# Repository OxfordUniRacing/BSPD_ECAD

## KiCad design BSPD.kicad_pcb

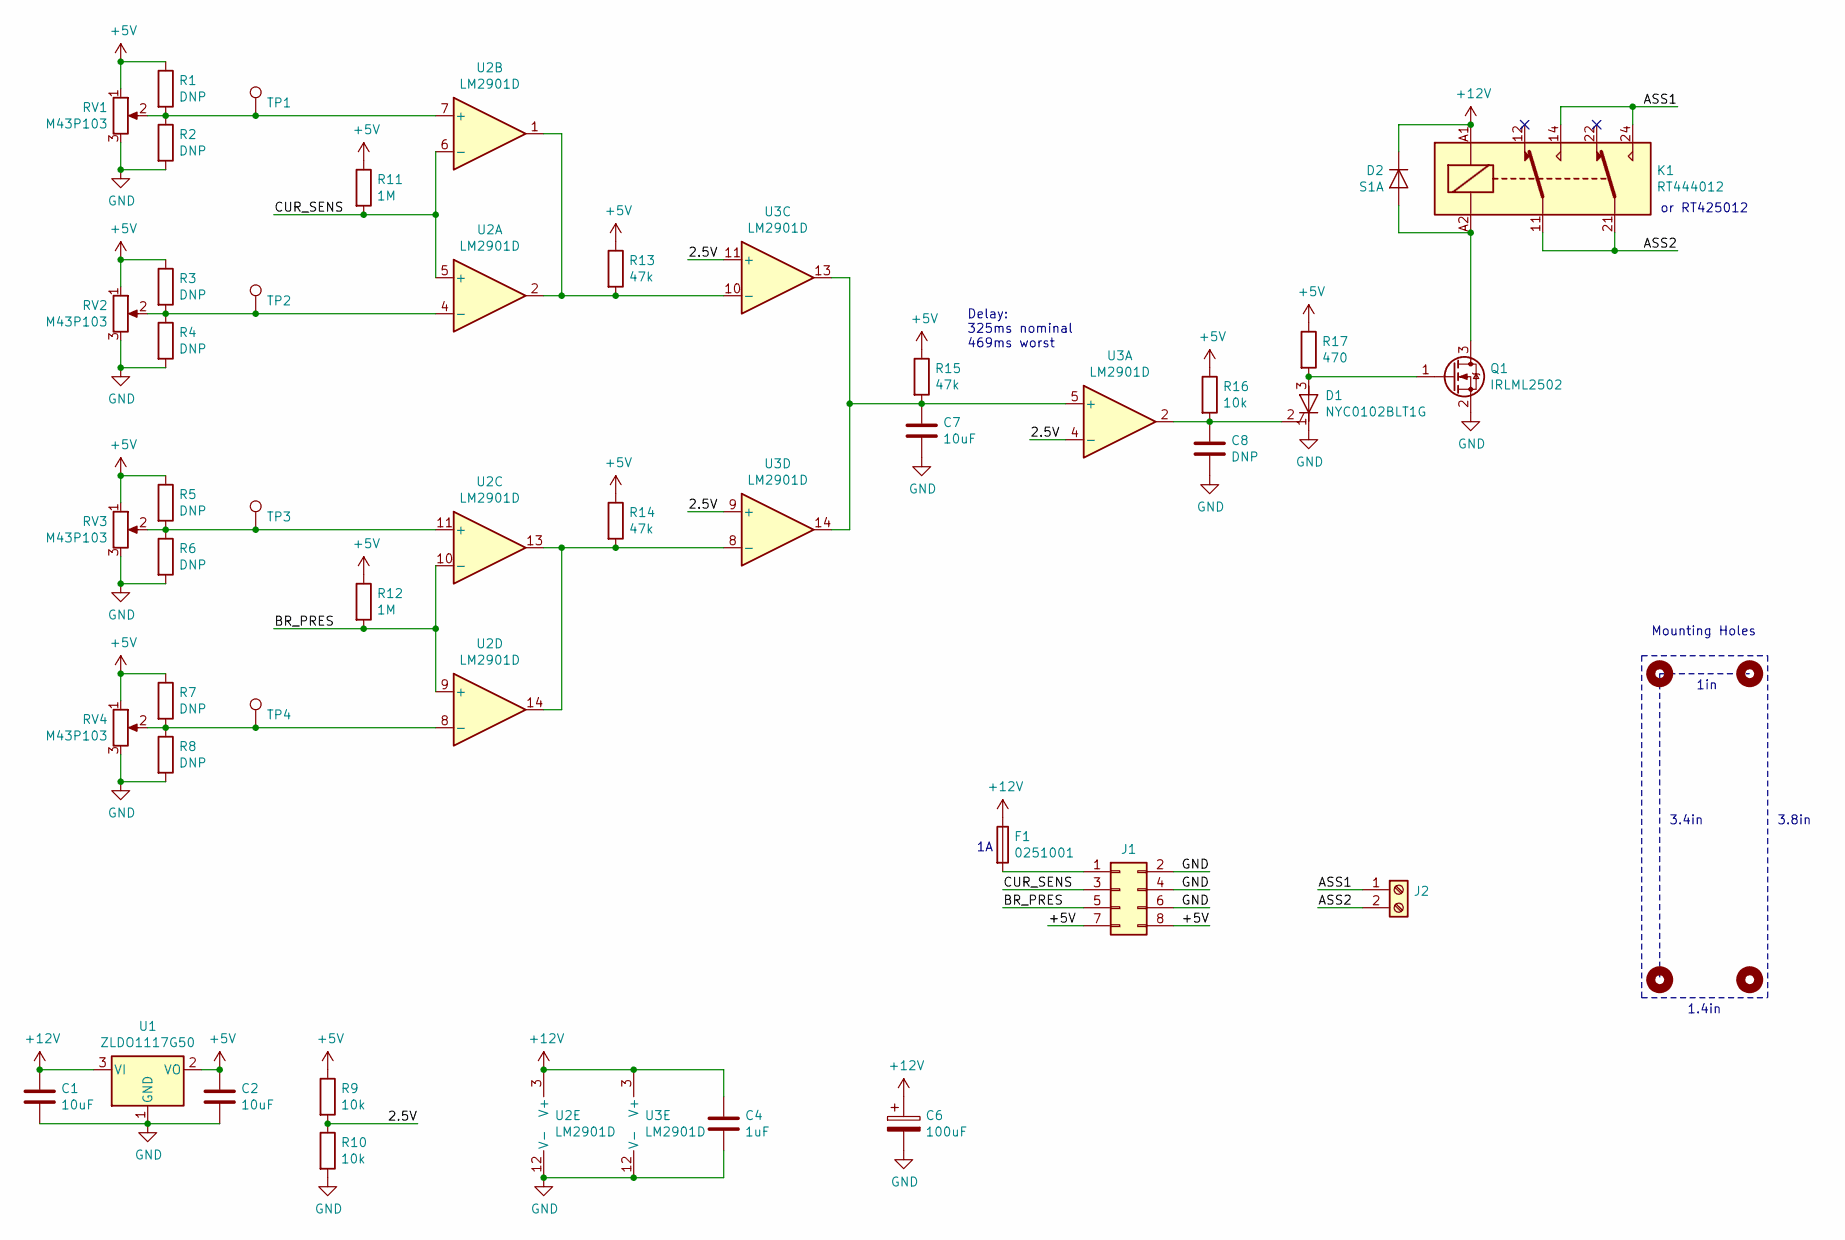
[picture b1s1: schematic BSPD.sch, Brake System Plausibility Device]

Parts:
C1, C2, C7: 10uF; C_0805_2012Metric_Pad1.15x1.40mm_HandSolder
C4: 1uF; C_0805_2012Metric_Pad1.15x1.40mm_HandSolder
C6: 100uF; CP_Radial_D6.3mm_P2.50mm
C8: DNP; C_0805_2012Metric_Pad1.15x1.40mm_HandSolder
D1: NYC0102BLT1G; SOT-23_Handsoldering
D2: S1A; D_SMA_Handsoldering
F1: 0251001; R_Axial_DIN0207_L6.3mm_D2.5mm_P10.16mm_Horizontal
H1, H2, H3, H4: MountingHole; MountingHole_3.2mm_M3_Pad
J1: Conn_02x04_Odd_Even; PinHeader_2x04_P2.54mm_Vertical_Shrouded
J2: Screw_Terminal_01x02; TerminalBlock_Phoenix_MKDS-1,5-2-5.08_1x02_P5.08mm_Horizont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
K1: RT444012; Relay_DPDT_Schrack-RT2-FormC_RM5mm
Q1: IRLML2502; SOT-23_Handsoldering
R1, R2, R3, R4, R5, R6, R7, R8: DNP; R_0805_2012Metric_Pad1.15x1.40mm_HandSolder
R9, R10, R16: 10k; R_0805_2012Metric_Pad1.15x1.40mm_HandSolder
R11, R12: 1M; R_0805_2012Metric_Pad1.15x1.40mm_HandSolder
R13, R14, R15: 47k; R_0805_2012Metric_Pad1.15x1.40mm_HandSolder
R17: 470; R_0805_2012Metric_Pad1.15x1.40mm_HandSolder
RV1, RV2, RV3, RV4: M43P103; Potentiometer_Vishay_43_Horizontal
TP1, TP2, TP3, TP4: TestPoint; TestPoint_Pad_D1.5mm
U1: ZLDO1117G50; SOT-223-3_TabPin2
U2, U3: LM2901D; SOIC-14_3.9x8.7mm_P1.27mm

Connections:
+5V: C2.1, J1.7, J1.8, R1.1, R3.1, R5.1, R7.1, R9.1, R11.1, R12.1, R13.1, R14.1, R15.1, R16.1, R17.1, RV1.1, RV2.1, RV3.1, RV4.1, U1.2 (VO)
+12V: C1.1, C4.1, C6.1, D2.1 (K), F1.1, K1.A1, U1.3 (VI), U2.3 (V+), U3.3 (V+); also elsewhere on the board
/2.5V: R9.2, R10.1, U3.4 (-), U3.9 (+), U3.11 (+)
/ASS1: J2.1, K1.14, K1.24
/ASS2: J2.2, K1.11, K1.21
/BR_PRES: J1.5, R12.2, U2.9 (+), U2.10 (-)
/CUR_SENS: J1.3, R11.2, U2.5 (+), U2.6 (-)
GND: C1.2, C2.2, C4.2, C6.2, C7.2, C8.2, D1.1 (K), J1.2, J1.4, J1.6, Q1.2 (S), R2.2, R4.2, R6.2, R8.2, R10.2, RV1.3, RV2.3, RV3.3, RV4.3, U1.1 (GND), U2.12 (V-), U3.12 (V-)
unnamed: C7.1, R15.2, U3.5 (+), U3.13, U3.14
unnamed: C8.1, D1.2 (G), R16.2, U3.2
unnamed: D1.3 (A), Q1.1 (G), R17.2
unnamed: D2.2 (A), K1.A2, Q1.3 (D)
unnamed 12: F1.2, J1.1; also elsewhere on the board
unnamed: R1.2, R2.1, RV1.2, TP1.1, U2.7 (+)
unnamed: R3.2, R4.1, RV2.2, TP2.1, U2.4 (-)
unnamed: R5.2, R6.1, RV3.2, TP3.1, U2.11 (+)
unnamed: R7.2, R8.1, RV4.2, TP4.1, U2.8 (-)
unnamed: R13.2, U2.1, U2.2, U3.10 (-)
unnamed: R14.2, U2.13, U2.14, U3.8 (-)

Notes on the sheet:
Delay: 325ms nominal 469ms worst
or RT425012
3.4in
1in
1.4in
3.8in
Mounting Holes

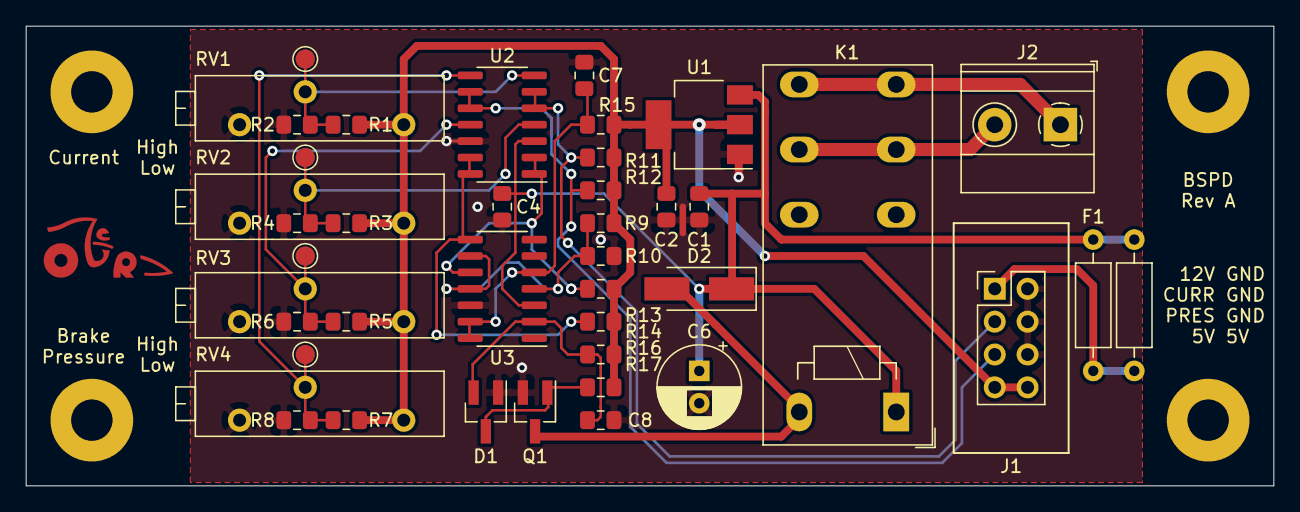
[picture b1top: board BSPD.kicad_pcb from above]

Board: 2 copper layers, 96.5 x 35.6 mm, 46 parts (0 on the bottom side), 19 nets.

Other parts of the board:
F1#2: 0251001; R_Axial_DIN0207_L6.3mm_D2.5mm_P10.16mm_Horizontal

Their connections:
+12V: F1#2.1; also elsewhere on the board
unnamed 12: F1#2.2; also elsewhere on the board

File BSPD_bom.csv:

"Id";"Designator";"Package";"Quantity";"Designation";"Supplier and ref";
1;"G***";"OUR-Logo";1;"LOGO";;;
2;"Q1";"SOT-23_Handsoldering";1;"IRLML2502";;;
3;"U3,U2";"SOIC-14_3.9x8.7mm_P1.27mm";2;"LM2901D";;;
4;"F1,F1";"R_Axial_DIN0207_L6.3mm_D2.5mm_P10.16mm_Horizontal";2;"0251001";;;
5;"TP4,TP3,TP2,TP1";"TestPoint_Pad_D1.5mm";4;"TestPoint";;;
6;"H4,H3,H2,H1";"MountingHole_3.2mm_M3_Pad";4;"MountingHole";;;
7;"J1";"PinHeader_2x04_P2.54mm_Vertical_Shrouded";1;"Conn_02x04_Odd_Even";;;
8;"D1";"SOT-23_Handsoldering";1;"NYC0102BLT1G";;;
9;"D2";"D_SMA_Handsoldering";1;"S1A";;;
10;"U1";"SOT-223";1;"ZLDO1117G50";;;
11;"RV4,RV3,RV2,RV1";"Potentiometer_Vishay_43_Horizontal";4;"M43P103";;;
12;"R17";"R_0805_2012Metric_Pad1.15x1.40mm_HandSolder";1;"470";;;
13;"R16,R10,R9";"R_0805_2012Metric_Pad1.15x1.40mm_HandSolder";3;"10k";;;
14;"R15,R14,R13";"R_0805_2012Metric_Pad1.15x1.40mm_HandSolder";3;"47k";;;
15;"R12,R11";"R_0805_2012Metric_Pad1.15x1.40mm_HandSolder";2;"1M";;;
16;"R8,R7,R6,R5,R4,R3,R2,R1";"R_0805_2012Metric_Pad1.15x1.40mm_HandSolder";8;"DNP";;;
17;"K1";"Relay_DPDT_Schrack-RT2-FormC_RM5mm";1;"RT444012";;;
18;"J2";"TerminalBlock_Phoenix_MKDS-1,5-2-5.08_1x02_P5.08mm_Horizontal";1;"Screw_Terminal_01x02";;;
19;"C8";"C_0805_2012Metric_Pad1.15x1.40mm_HandSolder";1;"DNP";;;
20;"C7,C2,C1";"C_0805_2012Metric_Pad1.15x1.40mm_HandSolder";3;"10uF";;;
21;"C6";"CP_Radial_D6.3mm_P2.50mm";1;"100uF";;;
22;"C4";"C_0805_2012Metric_Pad1.15x1.40mm_HandSolder";1;"1uF";;;

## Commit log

2019-11-14 rev a
2019-11-15 add logo
2019-12-31 update schematics
    Change regulator to ZLDO1117
2021-11-17 Added raw BOM export
